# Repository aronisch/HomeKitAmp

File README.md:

# HomeKitAmp
ARCHIVE : HomeKit + nRF24 Amp remote switch control (Abandoned version : see https://github.com/aronisch/PHAS/)

Based on HAP-NodeJS from KhaosT and nRF24 Libraries from tmrh20

Installation :
```
$ sudo apt-get install libavahi-compat-libdnssd-dev
```

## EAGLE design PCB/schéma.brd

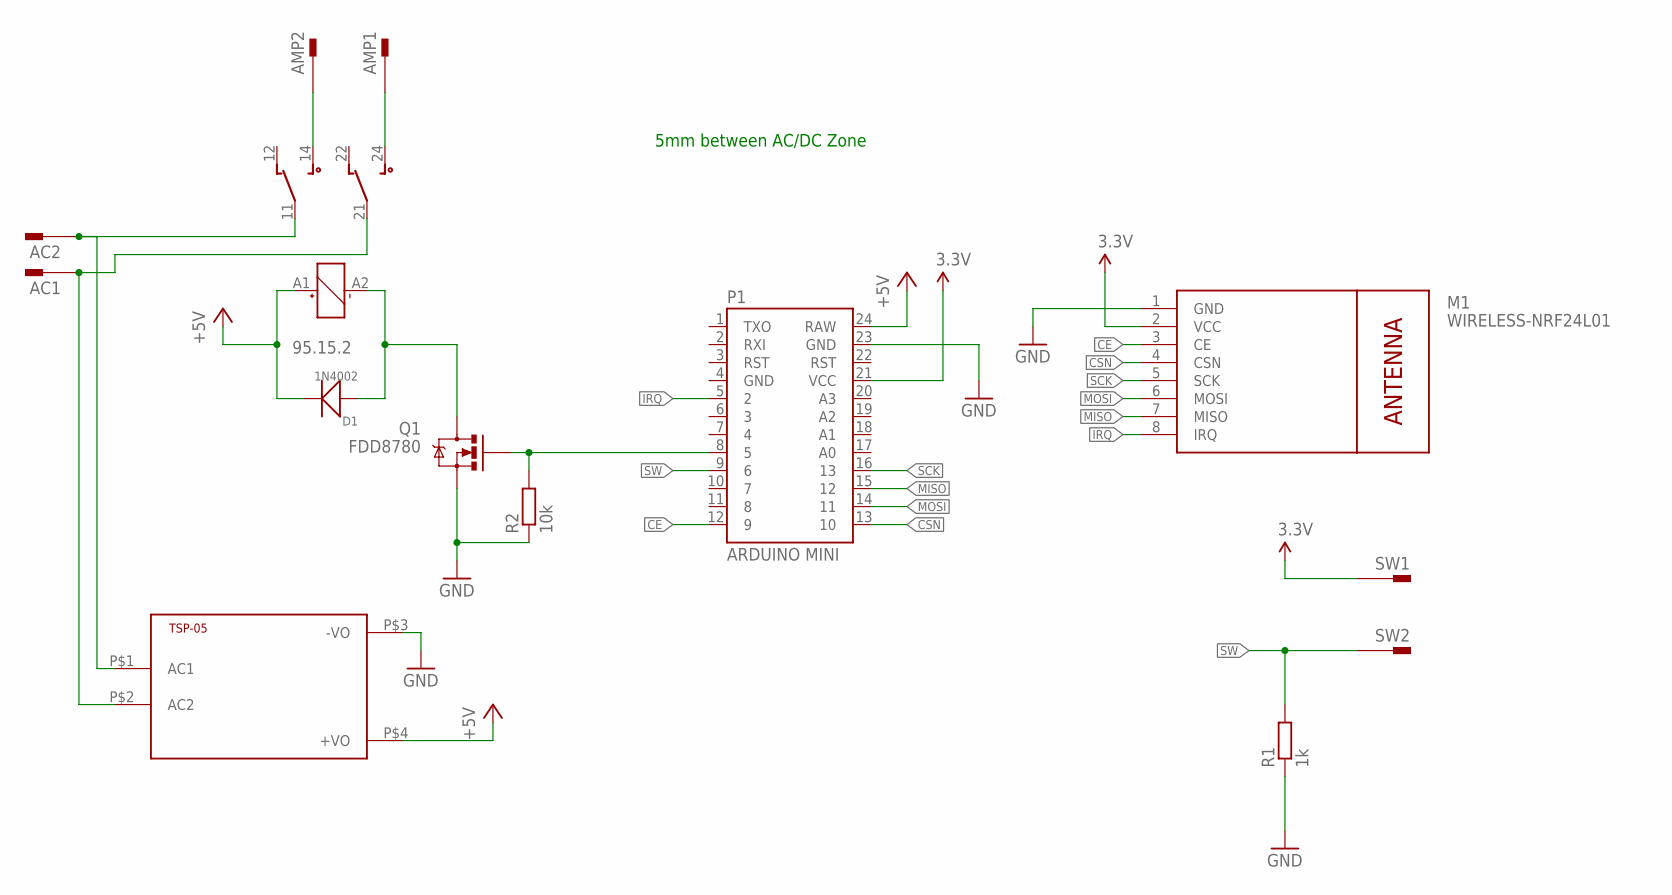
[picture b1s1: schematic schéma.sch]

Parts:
AC1, AC2: PIN2F061.100; F061.100
AMP1, AMP2: PIN2F061.100; F061.100
D1: 1N4002; DO-41
M1: WIRELESS-NRF24L01
P1: ARDUINO MINI; ARDUINO_MINI
Q1: FDD8780; DPAK
R1: 1k; 0207/10
R2: 10k; 0207/10
RL1: 95.15.2
SW1, SW2: PIN2F061.100; F061.100
TSP-05: HKLPM01

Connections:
3.3V: M1.2 (VCC), P1.21 (VCC), SW1.A1, SW1.A2
+5V: D1.2 (-), P1.24 (RAW), RL1.A1, TSP-05.P$4 (+VO)
CE: M1.3 (CE), P1.12 (9)
CSN: M1.4 (CSN), P1.13 (10)
GND: M1.1 (GND), P1.23 (GND), Q1.3 (S), R1.1, R2.1, TSP-05.P$3 (-VO)
IRQ: M1.8 (IRQ), P1.5 (2)
MISO: M1.7 (MISO), P1.15 (12)
MOSI: M1.6 (MOSI), P1.14 (11)
unnamed: AC1.A1, AC1.A2, RL1.21, TSP-05.P$2 (AC2)
unnamed: AC2.A1, AC2.A2, RL1.11, TSP-05.P$1 (AC1)
unnamed: AMP2.A1, AMP2.A2, RL1.14
unnamed: AMP1.A1, AMP1.A2, RL1.24
unnamed: P1.8 (5), Q1.1 (G), R2.2
unnamed: D1.1 (+), Q1.4 (D), RL1.A2
SCK: M1.5 (SCK), P1.16 (13)
SW: P1.9 (6), R1.2, SW2.A1, SW2.A2

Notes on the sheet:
5mm between AC/DC Zone

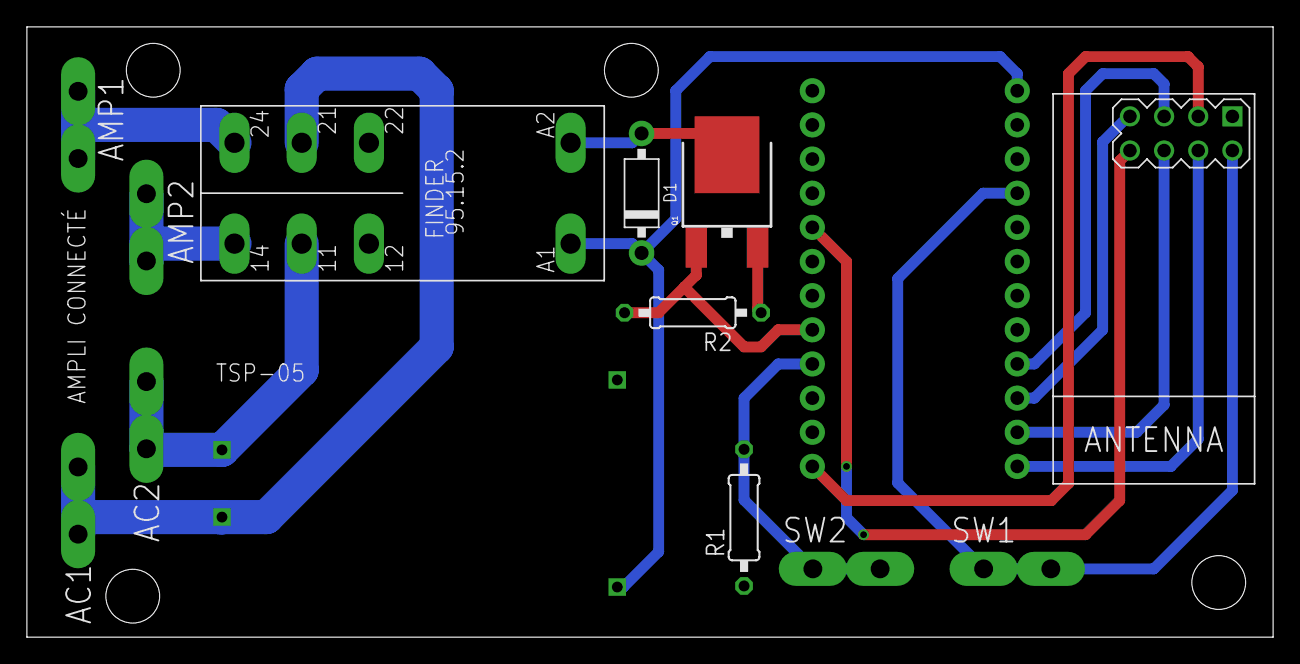
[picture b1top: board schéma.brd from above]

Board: 2 copper layers, 92.7 x 45.4 mm, 14 parts (0 on the bottom side), 16 nets.

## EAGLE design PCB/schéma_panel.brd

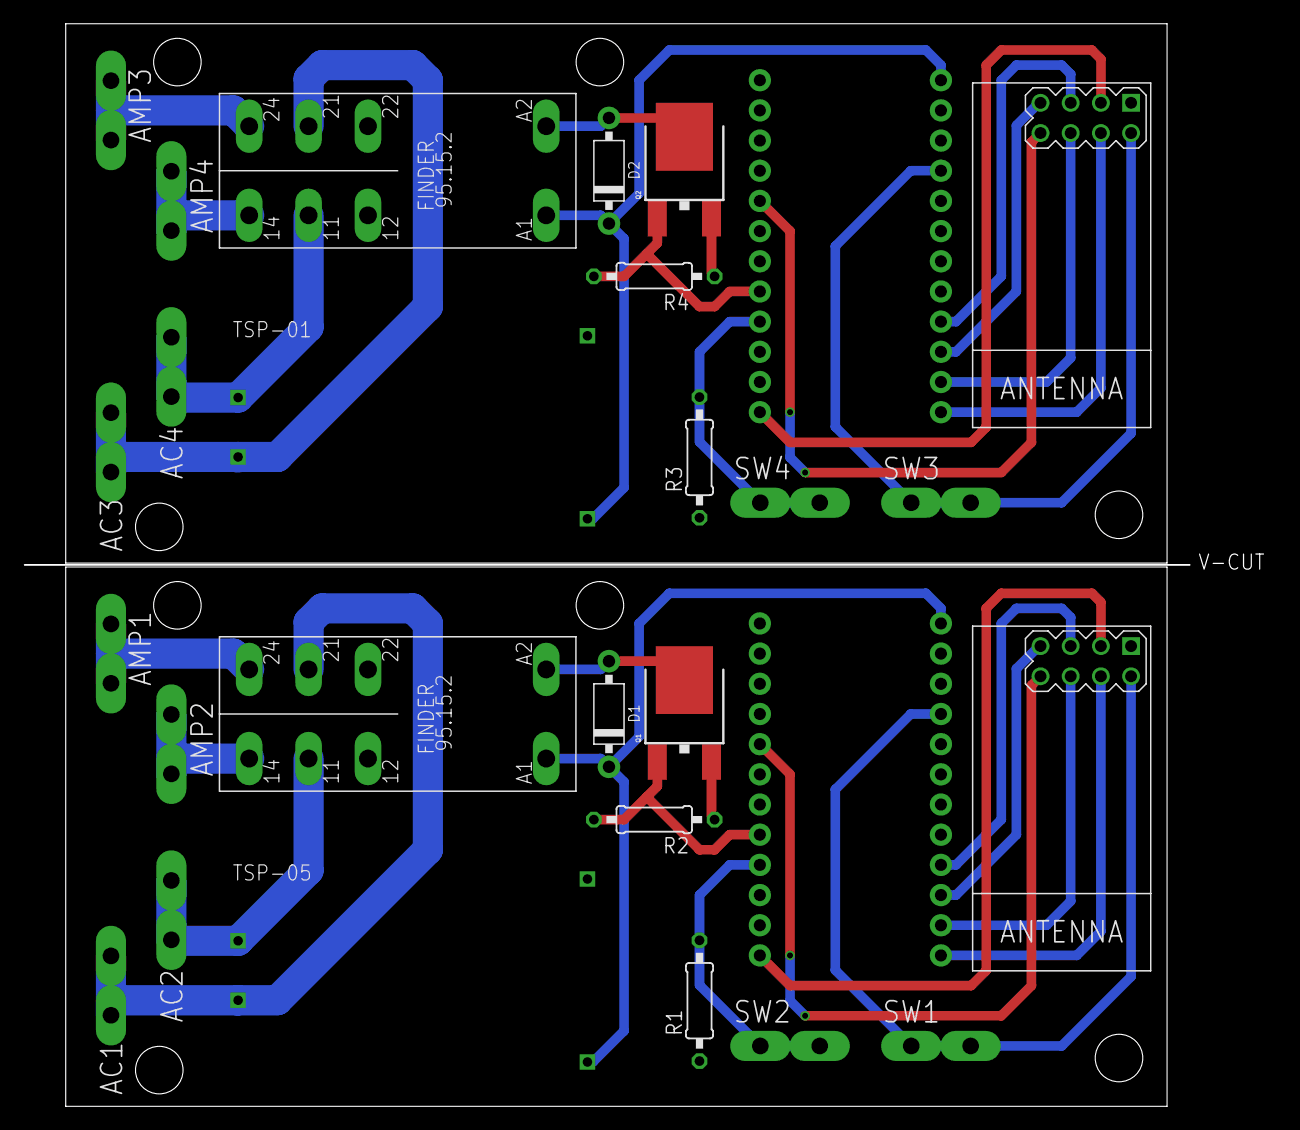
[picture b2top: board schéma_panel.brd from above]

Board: 2 copper layers, 105.3 x 91.0 mm, 28 parts (0 on the bottom side), 32 nets.

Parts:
AC1, AC2, AC3, AC4: F061.100
AMP1, AMP2, AMP3, AMP4: F061.100
D1, D2: 1N4002; DO-41
M1, M2: WIRELESS-NRF24L01
P1, P2: ARDUINO MINI; ARDUINO_MINI
Q1, Q2: FDD8780; DPAK
R1, R3: 1k; 0207/10
R2, R4: 10k; 0207/10
RL1, RL2: 95.15.2
SW1, SW2, SW3, SW4: F061.100
TSP-01, TSP-05: HKLPM01

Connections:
3.3V: M1.2, P1.21, SW1.A1, SW1.A2
3.3V1: M2.2, P2.21, SW3.A1, SW3.A2
+5V: D1.2, P1.24, RL1.A1, TSP-05.P$4
+5V1: D2.2, P2.24, RL2.A1, TSP-01.P$4
CE: M1.3, P1.12
CE1: M2.3, P2.12
CSN: M1.4, P1.13
CSN1: M2.4, P2.13
GND: M1.1, P1.23, Q1.3, R1.1, R2.1, TSP-05.P$3
GND1: M2.1, P2.23, Q2.3, R3.1, R4.1, TSP-01.P$3
IRQ: M1.8, P1.5
IRQ1: M2.8, P2.5
MISO: M1.7, P1.15
MISO1: M2.7, P2.15
MOSI: M1.6, P1.14
MOSI1: M2.6, P2.14
unnamed: AC1.A1, AC1.A2, RL1.21, TSP-05.P$2
unnamed: AC2.A1, AC2.A2, RL1.11, TSP-05.P$1
unnamed: AMP2.A1, AMP2.A2, RL1.14
unnamed: AMP1.A1, AMP1.A2, RL1.24
unnamed: P1.8, Q1.1, R2.2
unnamed: D1.1, Q1.4, RL1.A2
unnamed: AC4.A1, AC4.A2, RL2.11, TSP-01.P$1
unnamed: AC3.A1, AC3.A2, RL2.21, TSP-01.P$2
unnamed: AMP4.A1, AMP4.A2, RL2.14
unnamed: AMP3.A1, AMP3.A2, RL2.24
unnamed: D2.1, Q2.4, RL2.A2
unnamed: P2.8, Q2.1, R4.2
SCK: M1.5, P1.16
SCK1: M2.5, P2.16
SW: P1.9, R1.2, SW2.A1, SW2.A2
SW1: P2.9, R3.2, SW4.A1, SW4.A2

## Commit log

2017-11-17 creation of Arduino ino program file and first C++ file
2017-11-17 add nRF24 Libraries
2017-11-18 first attempt of an arduino program with a small C++ program for the RPi
2017-11-18 fix Makefile
2017-11-18 try fixing makefile
2017-11-18 fix variable name and clean in makefile
2017-11-18 fix Makefile with corresponding library and change pin in the program for RPi2
2017-11-18 send state until successful reception
2017-11-19 add PCB Files
2017-11-19 rename Arduino program folder
2017-11-19 first attempt of a nodejs addon
2017-11-19 add a simple amp accessory based on outlet_accessory from HAP-NodeJS
2017-11-19 copy of Core.js from HAP-NodeJS
2017-11-19 fix version number and set as private
2017-11-19 fix syntax error
2017-11-19 fix hap-nodejs paths
2017-11-19 fix node-persist path
2017-11-19 fix paths
2017-11-19 add missing streaming-worker module
2017-11-19 rename accessory file for hap
2017-11-19 fix missing radio starting method
2017-11-20 fix logs
2017-11-20 set new status when receiving from radio
2017-11-20 add logs for debugging
2017-11-20 fix set new status
2017-11-26 add time in logs

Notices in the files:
parts and their libraries:
nRF24: Released under the Creative Commons Attribution 4.0 International License: http://creativecommons.org/licenses/by/4.0
SparkFun-Boards: Licensing: Creative Commons ShareAlike 4.0 International - https://creativecommons.org/licenses/by-sa/4.0
